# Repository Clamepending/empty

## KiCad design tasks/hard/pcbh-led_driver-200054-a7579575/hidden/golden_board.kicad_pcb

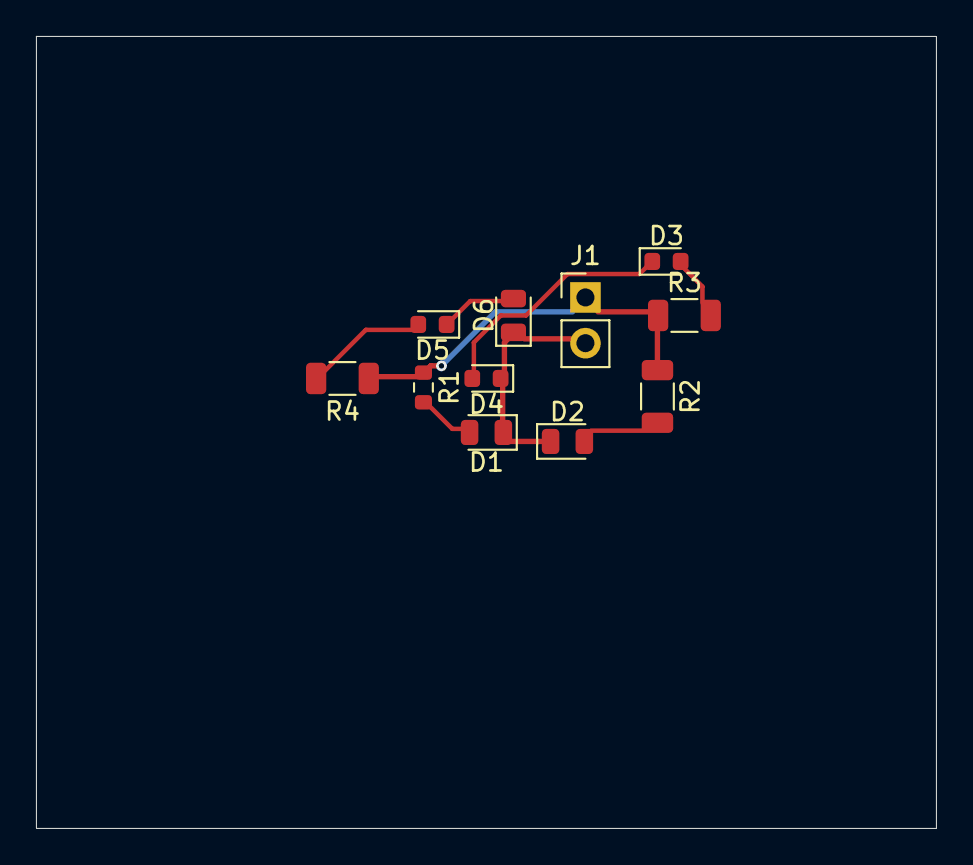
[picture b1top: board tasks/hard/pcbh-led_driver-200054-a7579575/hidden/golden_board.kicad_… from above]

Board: 2 copper layers, 50.0 x 44.0 mm, 11 parts (0 on the bottom side), 8 nets.

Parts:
D1, D2, D6: LED_0805_2012Metric
D3, D4, D5: LED_0603_1608Metric
J1: PinHeader_1x02_P2.54mm_Vertical
R1: 5.1k; R_0603_1608Metric
R2: 470; R_1206_3216Metric
R3: 820; R_1206_3216Metric
R4: 510; R_1206_3216Metric

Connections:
CH1_0: D1.2, R1.2
CH2_0: D2.2, R2.2
CH3_0: D3.2, R3.2
CH3_1: D3.1, D4.2
CH4_0: D5.2, R4.2
CH4_1: D5.1, D6.2
GND: D1.1, D2.1, D4.1, D6.1, J1.2
VS: J1.1, R1.1, R2.1, R3.1, R4.1

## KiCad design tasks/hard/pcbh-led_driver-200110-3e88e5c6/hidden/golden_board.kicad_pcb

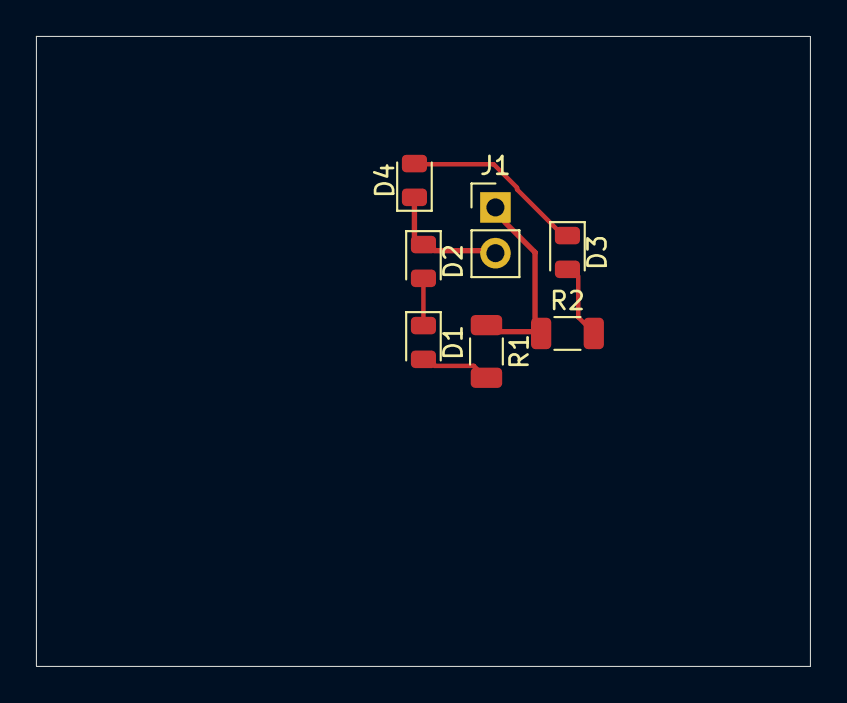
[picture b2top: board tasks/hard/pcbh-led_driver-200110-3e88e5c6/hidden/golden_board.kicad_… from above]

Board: 2 copper layers, 43.0 x 35.0 mm, 7 parts (0 on the bottom side), 6 nets.

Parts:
D1, D2, D3, D4: LED_0805_2012Metric
J1: PinHeader_1x02_P2.54mm_Vertical
R1: 3.9k; R_1206_3216Metric
R2: 390; R_1206_3216Metric

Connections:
CH1_0: D1.2, R1.2
CH1_1: D1.1, D2.2
CH2_0: D3.2, R2.2
CH2_1: D3.1, D4.2
GND: D2.1, D4.1, J1.2
VS: J1.1, R1.1, R2.1
